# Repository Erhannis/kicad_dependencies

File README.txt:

Some component modules for KiCAD projects, like a micro usb power/data connection, or an eeprom chip with associated caps and resistors.  Comes as sheets, with separate areas of 4-layer PCB, and everything should be annotated with JLCPCB component IDs so you can export with their kicad plugin and it should autofill all the parts for assembly.

To use:
Copy the .kicad_sch file you want, into your project.
In KiCAD, copy the sheet block you want from this project into your project.
In KiCAD, ensure your project has 4 layers (MAYBE you can get it to work otherwise) then copy the corresponding chunk of PCB you want.
THEN "update pcb from schematic", to ensure everything synced up.

IF YOU ADD A MODULE, or rename a reference, you may need to run the vscode js script (see the nur::script extension) to get the refs to copy right - it updates all the labels from the pcb. ...I think.  I forget, now.  Then it removes the "instances" blocks, which don't seem to be necessary and can apparently gunk up the refs??  Commit your files before running the script.

If a part won't load for you, try `pip install easyeda2kicad` and `easyeda2kicad --lcsc_id LCSC_ID_HERE --full`, and adding its symbol/footprint folder to kicad.  I sometimes feel like it would be better to find a kicad built-in footprint or whatever, but it's just so easy....  (I don't think I've used this yet in this repo, but it's just a matter of time, haha.)

So far these things are like, MIT or CERN OHL v2 P (even if I've had to find a second source for the same decisions in a few places).

Notes:
(There may be bugs not listed here.)
inverted_regulator_12v doesn't quite manage an amp; it thermal cycles at 0.85A.  0.8A seemed to work, though you might do 0.7A to be safe.  If you added a proper heat sink it might manage MORE than 1A, haha.  Maybe you could add vias to a plane; depends on if the back is grounded; gnd is connected to -12V after all.
power_cell_18650_3s
  successfully provides several amps at ~12V
  successfully shuts down when batteries dip below 2.7V*3
  successfully switch on/off
  BUG: DO NOT short the output.  It kills the on/off transistor which shorts mostly closed, preventing the controller from turning off the circuit.  Further shorts can cause the on/off transistor to catch fire.
  BUG: it prevents overcurrent when charging (only lightly tested), but does not actually regulate the charging current!  Which means it can't charge the battery without external current control.  Sigh.
amp12v2a does not work.  Huge noise on the output.  I don't know why, I've been trying to get similar circuits to work for weeks.

-Erhannis

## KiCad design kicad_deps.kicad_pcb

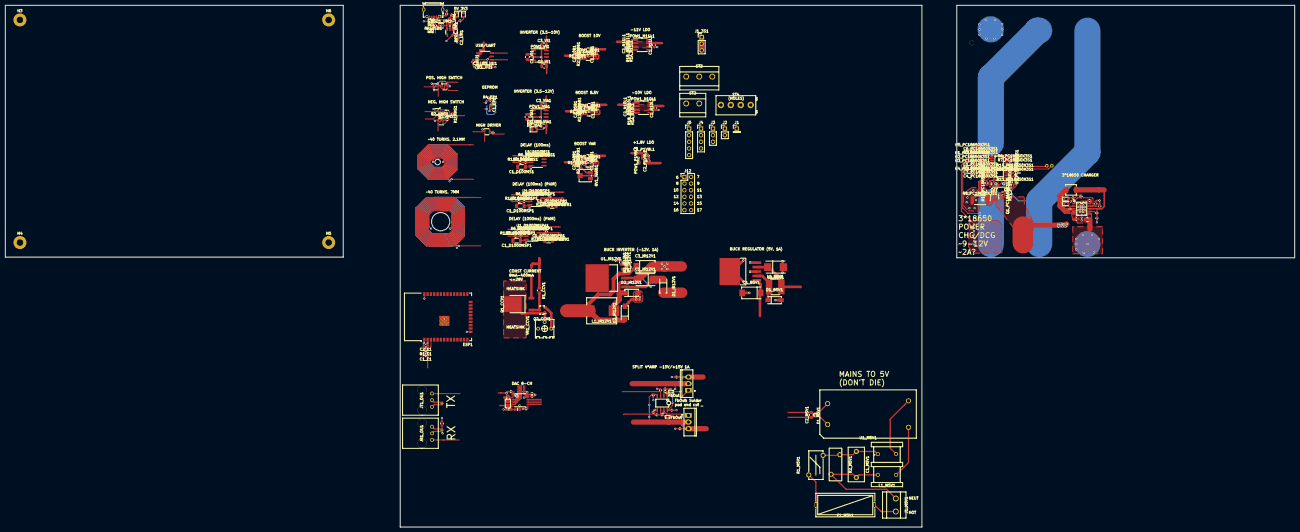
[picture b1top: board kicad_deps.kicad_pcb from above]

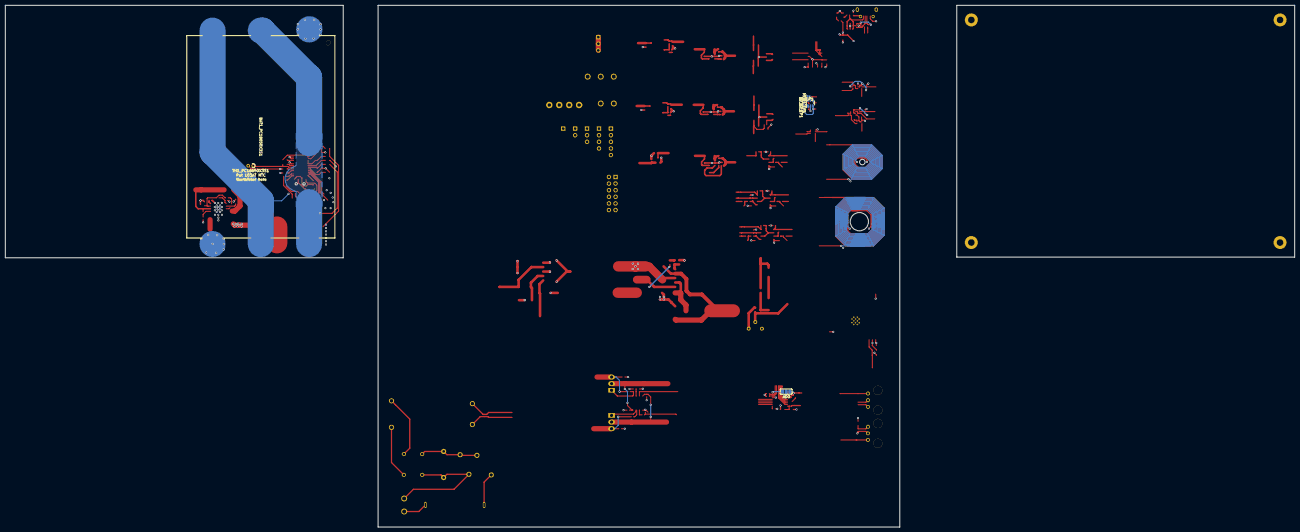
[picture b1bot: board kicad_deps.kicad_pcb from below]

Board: 4 copper layers, 200.0 x 200.0 mm, 232 parts (7 on the bottom side), 149 nets.

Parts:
BAT1_PC18650X3S1: BH-18650-B5BA016; BAT-SMD_BH-18650-B5BA016
C1_10B1, C1_85B1, C1_C18650X3S1, C1_N10L1, C1_N11L1, C1_P1V8L1, C1_VARB1, C2_10B1, C2_85B1, C2_C18650X3S1, C2_N10L1, C2_N11L1, C2_P1V8L1, C2_VARB1, C5_C18650X3S1: 10uF; C_0603_1608Metric
C1_B5V1: 100uF; CAP-SMD_L7.3-W4.3-R-RD
C1_D100MS1, C1_D100MSP1, C1_D100MSPB1, C1_D1000MSP1, C1_D1000MSPB1: 100uF; C_1206_3216Metric
C1_E1, C1_UU1, C2_UU1, C3_UU1, C5_PC18650X3S1, C6_PC18650X3S1: 1uF; C_0603_1608Metric
C1_EP1, C1_OU1, C2_OU1, C3_C18650X3S1: 100nF; C_0402_1005Metric
C1_IR12V1: 68uF; CASE-D_7343
C1_M5V1: 100nF/275V; C_Rect_L13.0mm_W6.0mm_P10.00mm_FKS3_FKP3_MKS4
C1_PC18650X3S1, C2_IR12V1, C2_PC18650X3S1, C3_PC18650X3S1, C4_PC18650X3S1: 0.1uF; C_0603_1608Metric
C1_S4AN15P151A1, C2_S4AN15P151A1: 0.1uF; C_0402_1005Metric
C1_UM1, C1_VI1, C1_VIA1, C2_M5V1, C2_UM1, C2_VI1, C2_VIA1, C3_VI1, C3_VIA1: 10uF; C_0805_2012Metric
C2_B5V1: 470uF; CASE-D_7343
C2_E1: 22uF; C_0603_1608Metric
C3_D8C1: 1uF; 0603-NO
C3_IR12V1: 47uF; CAP-SMD_L7.3-W4.3-FD
C4_C18650X3S1: C; C_0805_2012Metric
C4_D8C1: 0.1uF; 0603-NO
D1_10B1, D1_85B1, D1_VARB1, D1_VIA1: D_Schottky; D_0402_1005Metric
D1_B5V1, D1_IR12V1, D2_IR12V1, D3_IR12V1: SS54_C22452; SMA_L4.4-W2.8-LS5.4-R-RD
D1_M5V1: ESD9B5.0ST5G; D_SOD-923
D1_UM1: LED(R); LED_0603_1608Metric
D2_UM1: LED(G); LED_0603_1608Metric
D2_VIA1: D; D_0805_2012Metric
ESD1_UM1: USBLC6-2P6; SOT-666
ESP1: ESP32-WROOM-32D
F1_M5V1: Fuse transparent seat; FUSE-TH_L24.5-W9.8-P22.5
FB1_D8C1: FERRITE; 0603-NO
H1, H2: MountingHole; MountingHole_2.1mm
H3, H4, H5, H6: MountingHole_Pad; MountingHole_2.5mm_Pad
J1: Conn_01x01_Pin; PinHeader_1x01_P2.54mm_Vertical
J1_3S1, J3: Conn_01x03_Pin; PinHeader_1x03_P2.54mm_Vertical
J1_M5V1: XY126V-5.0-2P; CONN-TH_XY126V-5.0-2P
J2: Conn_01x02_Pin; PinHeader_1x02_P2.54mm_Vertical
J4: Conn_01x04_Pin; PinHeader_1x04_P2.54mm_Vertical
J5: Conn_01x05_Pin; PinHeader_1x05_P2.54mm_Vertical
J12: Conn_02x06_Odd_Even; PinHeader_2x06_P2.54mm_Vertical
JP1_S4AN15P151A1, JP2_S4AN15P151A1: SolderJumper_2_Open; SolderJumper-2_P0.5mm_Open_Pad0.5x0.5mm
JR1_OU1: ZGY135/T9(PLR); OPTO-TH_ZGY135-T9-PLR
JT1_OU1: ZGY133/T9(PLT); OPTO-TH_ZGY135-T9-PLR
L1_10B1, L1_85B1, L1_VARB1: L 10uH; L_0805_2012Metric
L1_B5V1: 330uH; IND-SMD_L6.0-W6.0_FNR60XXS
L1_C18650X3S1: SL0420-2R2M; IND-SMD_L4.5-W4.1_GSSM0420
L1_IR12V1: 33uH, 4A; IND-SMD_L11.5-W10.0_FXL1040
L1_M5V1: UU9.8-20MH; FILTER-TH_4P-L17.0-W12.0-P7.00-D0.6-S8.00
L1_OU1: 47uH; L_0603_1608Metric
LED1_C18650X3S1: LED(R); LED_0603_1608Metric
LED2_C18650X3S1: LED(B); LED_0603_1608Metric
MEM1_EP1: 93LCxxB; SOT-23-6
POW1_10B1, POW1_85B1, POW1_VARB1: LM27313XMF; SOT-23-5
POW1_N10L1, POW1_N11L1: LM337L_SO8; SOIC-8_3.9x4.9mm_P1.27mm
POW1_P1V8L1: APE8865N-18-HF-3; SOT-23
POW1_VI1, POW1_VIA1: TC7662Bx0A; SOIC-8_3.9x4.9mm_P1.27mm
Q1_CCV1: MOT13003D; TO-252-3_L6.5-W5.9-P4.60-LS10.0-BL
Q1_HD1, Q1_NHS1, Q1_PHS1, Q2_NHS1, Q2_PHS1, Q3_NHS1: BSD235C; SOT-363_SC-70-6
Q1_PC18650X3S1: FS8205A_C908265; SOT-23-6_L2.9-W1.6-P0.95-LS2.8-BR
Q1_S4AN15P151A1: IRF540NPBF; TO-220-3_L10.0-W4.5-P2.54-L
Q2_CCV1: SS8050; SOT-23-3
Q2_S4AN15P151A1: IRF9540NPBF; TO-220-3_L10.0-W4.5-P2.54-L
R1A_N10L1: R 1.6k 1%; R_0402_1005Metric
R1A_N11L1: R 1.8k 1%; R_0402_1005Metric
R1B_N10L1, R1B_N11L1: R 75 1%; R_0402_1005Metric
R1_10B1, R1_85B1, R1_VARB1: R 100k 1%; R_0402_1005Metric
R1_C18650X3S1: 37k; R_0402_1005Metric
R1_CCV1: 3.3k; R_0805_2012Metric
R1_D8C1, R1_D1000MSP1, R1_D1000MSPB1, R1_HD1, R1_S4AN15P151A1, R2_C18650X3S1, R2_D100MS1, R2_D100MSP1, R2_D100MSPB1, R2_D1000MSP1, R2_D1000MSPB1, R4_D100MS1, R4_D100MSP1, R4_D1000MSP1, R4_S4AN15P151A1, R5_D100MS1, R5_D100MSP1, R5_D1000MSP1, R5_S4AN15P151A1, R6_S4AN15P151A1: 10k; R_0402_1005Metric
R1_D100MS1, R1_D100MSP1, R1_D100MSPB1, R3_C18650X3S1: 1k; R_0402_1005Metric
R1_E1, R6_PC18650X3S1, R7_PC18650X3S1, R15_PC18650X3S1: 10k; R_0603_1608Metric
R1_EP1, R2_EP1, R4_EP1: 10K; R_0402_1005Metric
R1_IR12V1, R2_IR12V1: 47k; R_0603_1608Metric
R1_M5V1: 5D-9_C332361; RES-TH_L11.0-W5.5-P7.50-D0.8-S5.50
R1_NHS1, R2_S4AN15P151A1, R3_NHS1: 30k; R_0402_1005Metric
R1_PC18650X3S1, R2_PC18650X3S1, R3_PC18650X3S1, R4_PC18650X3S1: 75ohm; R_0603_1608Metric
R1_UM1: 1M; R_0402_1005Metric
R2_10B1: R 14k 1%; R_0402_1005Metric
R2_85B1: R 16k 1%; R_0402_1005Metric
R2_D8C1, R3_D8C1, R4_D8C1: 4.7k; R_0402_1005Metric
R2_M5V1: 471KD10; RES-TH_L12.5-W4.8-P7.50-D1.2-S3.40
R2_N10L1, R2_N11L1: R 240 1%; R_0402_1005Metric
R2_NHS1: 50k; R_0402_1005Metric
R2_UM1, R3_UM1: 27; R_0402_1005Metric
R2_VARB1: R 4.53k 1%; R_0402_1005Metric
R3_D100MS1, R3_D100MSP1, R3_D100MSPB1, R3_D1000MSP1, R3_D1000MSPB1: 10M; R_0402_1005Metric
R3_EP1: 2K; R_0402_1005Metric
R3_S4AN15P151A1: 40k; R_0402_1005Metric
R4_C18650X3S1, R5_C18650X3S1, R6_D100MS1, R6_D100MSP1, R6_D100MSPB1, R6_D1000MSP1, R6_D1000MSPB1, R7_S4AN15P151A1, R8_S4AN15P151A1: 100k; R_0402_1005Metric
R4_UM1, R5_UM1: 330; R_0402_1005Metric
R5_PC18650X3S1, R11_PC18650X3S1: 1k; R_0603_1608Metric
R6_C18650X3S1: 3k; R_0402_1005Metric
R8_PC18650X3S1: 10mOhm; R_2512_6332Metric
R9_PC18650X3S1, R10_PC18650X3S1: 1M; R_0603_1608Metric
R12_PC18650X3S1: 4.42k; R_0603_1608Metric
R13_PC18650X3S1: 450k; R_0402_1005Metric
R14_PC18650X3S1: 294k; R_0603_1608Metric
REG1_UM1: AP2112K-3.3; SOT-23-5
RP_USB1: MICROXNJ; MICRO-USB-SMD_MICROXNJ
RV1_VARB1: 100k R_Potentiometer; Potentiometer_Bourns_3314J_Vertical
SJ1_D8C1: SOLDERJUMPER_CLOSED; SOLDERJUMPER_CLOSEDWIRE
SJ3_D8C1: SOLDERJUMPER_2WAY; SOLDERJUMPER_2WAY_OPEN_NOPASTE
ST2: XY126V-5.0-2P; CONN-TH_XY126V-5.0-2P
ST3: XY126V-5.0-3P; CONN-TH_XY126V-5.0-3P
ST4: DB125-3.81-4P; CONN-TH_DB125-3.81-4P
SW1_PC18650X3S1: MSS3-Q-T/R; SW-SMD_MSS3-Q-T-R
TH1_PC18650X3S1: 103AT NTC 10k +-3%; R_Axial_DIN0204_L3.6mm_D1.6mm_P1.90mm_Vertical
U1_B5V1: LM2575S-5.0/TR; TO-263-5_L10.6-W9.6-P1.70-LS15.9-BR
U1_C18650X3S1: LGS5523; ESSOP-10_L4.9-W3.9-P1.00-LS6.0-BL-EP
U1_D100MS1, U1_D100MSP1, U1_D1000MSPA1: LM358; SOIC-8_3.9x4.9mm_P1.27mm
U1_IR12V1: LM2575HVS-12_C347430; TO-263-5_L10.2-W9.2-P1.70-BR
U1_M5V1: EC03-S05_C2840800; PWRM-TH_EC03-S05
U1_PC18650X3S1: BQ7791502PWR; TSSOP-24_L7.8-W4.4-P0.65-LS6.4-BL_1
U1_S4AN15P151A1: LM358; SOIC-8_L5.0-W4.0-P1.27-LS6.0-BL
U1_UU1: HT42B534_8SOP; SOP-8_3.9x4.9mm_P1.27mm
VR1_CCV1: 3362P-1-101LF; RES-ADJ-TH_3362P-1-104LF
X1_D8C1: DAC7578PW; TSSOP16

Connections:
+3V3: C1_EP1.1, C1_UU1.1, C2_E1.1, C2_OU1.2, C2_UM1.1, C3_UU1.1, ESP1.2 (VDD), JT1_OU1.2 (VCC), L1_OU1.1, MEM1_EP1.6 (VCC), R1_E1.2, R1_EP1.2, R2_EP1.2, R4_EP1.2, R5_UM1.1, REG1_UM1.5 (VOUT), U1_UU1.3 (VDDIO), U1_UU1.7 (VDD)
/DC Boost 8.5v/VIN: C1_85B1.2, L1_85B1.1, POW1_85B1.4 (EN), POW1_85B1.5 (VIN)
/DC Boost 8.5v/VOUT: C2_85B1.2, D1_85B1.1 (K), R1_85B1.1
/DC Boost 10v/VIN: C1_10B1.2, L1_10B1.1, POW1_10B1.4 (EN), POW1_10B1.5 (VIN)
/DC Boost 10v/VOUT: C2_10B1.2, D1_10B1.1 (K), R1_10B1.1
/DC Boost Var/VIN: C1_VARB1.2, L1_VARB1.1, POW1_VARB1.4 (EN), POW1_VARB1.5 (VIN)
/DC Boost Var/VOUT: C2_VARB1.2, D1_VARB1.1 (K), R1_VARB1.1
/Delay (100ms) (pair)/VDD: R4_D100MSP1.1, U1_D100MSP1.8 (V+)
/Delay (100ms) (pair)/VOUT1: R3_D100MSP1.2, R6_D100MSP1.2, U1_D100MSP1.1
/Delay (100ms) (pair)/VOUT2: R3_D100MSPB1.2, R6_D100MSPB1.2, U1_D100MSP1.7
/Delay (100ms)/VDD: R4_D100MS1.1, U1_D100MS1.8 (V+)
/Delay (100ms)/VOUT1: R3_D100MS1.2, R6_D100MS1.2, U1_D100MS1.1
/Delay (1000ms) (pair)/VDD: R4_D1000MSP1.1, U1_D1000MSPA1.8 (V+)
/Delay (1000ms) (pair)/VOUT1: R3_D1000MSP1.2, R6_D1000MSP1.2, U1_D1000MSPA1.1
/Delay (1000ms) (pair)/VOUT2: R3_D1000MSPB1.2, R6_D1000MSPB1.2, U1_D1000MSPA1.7
/EEPROM/CLK: MEM1_EP1.4 (CLK), R4_EP1.1
/EEPROM/CS#: MEM1_EP1.5 (CS), R1_EP1.1
/EEPROM/DATA: MEM1_EP1.3 (DI), R3_EP1.1
/ESP32/EN: C1_E1.1, ESP1.3 (EN), R1_E1.1
/High Driver/V_IN: Q1_HD1.4 (SP), R1_HD1.2
/Mains to 5V/+5V: C2_M5V1.2, D1_M5V1.1 (A1), U1_M5V1.5 (+Vo)
/Mains to 5V/GND: C2_M5V1.1, D1_M5V1.2 (A2), U1_M5V1.3 (-Vo)
/Mains to 5V/HOT: F1_M5V1.1, J1_M5V1.2
/Mains to 5V/NEUTRAL: C1_M5V1.2, J1_M5V1.1, L1_M5V1.4, R2_M5V1.2
/Negative High Switch/TREF: Q1_NHS1.4 (SP), Q2_NHS1.4 (SP)
/Negative High Switch/TRIG: Q1_NHS1.2 (GN), Q1_NHS1.5 (GP)
/Negative High Switch/V_IN: Q2_NHS1.1 (SN), Q3_NHS1.1 (SN), R1_NHS1.2, R3_NHS1.2
/Negative LDO -10v/-VIN: C1_N10L1.2, POW1_N10L1.2 (VI), POW1_N10L1.3 (VI), POW1_N10L1.6 (VI), POW1_N10L1.7 (VI)
/Negative LDO -10v/-VOUT: C2_N10L1.2, POW1_N10L1.1 (VO), R2_N10L1.2
/Negative LDO -11v/-VIN: C1_N11L1.2, POW1_N11L1.2 (VI), POW1_N11L1.3 (VI), POW1_N11L1.6 (VI), POW1_N11L1.7 (VI)
/Negative LDO -11v/-VOUT: C2_N11L1.2, POW1_N11L1.1 (VO), R2_N11L1.2
/Positive High Switch/TRIG: Q1_PHS1.2 (GN), Q1_PHS1.5 (GP)
/Positive High Switch/V_OUT: Q2_PHS1.3 (DP), Q2_PHS1.6 (DN)
/Positive LDO +1.8v/VIN: C1_P1V8L1.1, POW1_P1V8L1.3 (VI)
/Positive LDO +1.8v/VOUT: C2_P1V8L1.1, POW1_P1V8L1.2 (VO)
/Splitter(3)/IN: J1_3S1.1, J1_3S1.2, J1_3S1.3
/USB Micro B/+5V: C1_UM1.1, ESD1_UM1.5 (VBUS), R4_UM1.1, REG1_UM1.1 (VIN), REG1_UM1.3 (EN), RP_USB1.1 (VBUS)
/Voltage Inverter alt/V+: C3_VIA1.2, POW1_VIA1.8 (V+)
/Voltage Inverter alt/V-: C2_VIA1.2, D1_VIA1.2 (A), D2_VIA1.2 (A), POW1_VIA1.5 (VOUT)
/Voltage Inverter/V+: C3_VI1.2, POW1_VI1.8 (V+)
/Voltage Inverter/V-: C2_VI1.2, POW1_VI1.5 (VOUT)
/buck_5v/Vin: C1_B5V1.1, U1_B5V1.1 (VIN)
/buck_5v/Vout: C2_B5V1.1, L1_B5V1.2, U1_B5V1.4 (FB)
/charger_18650_3s/Vin: C5_C18650X3S1.1, L1_C18650X3S1.1, R1_C18650X3S1.1, U1_C18650X3S1.8 (VIN)
/dac8c/SCL: R4_D8C1.2, X1_D8C1.16 (SCL)
/dac8c/SDA: R3_D8C1.2, X1_D8C1.15 (SDA)
/dac8c/VREFIN: C3_D8C1.1, C4_D8C1.1, SJ1_D8C1.1, X1_D8C1.8 (VREFIN)
/dac8c/Vcc: FB1_D8C1.2, R1_D8C1.1, R2_D8C1.1, R3_D8C1.1, R4_D8C1.1, SJ3_D8C1.1, X1_D8C1.3 (AVDD)
/dac8c/~CLR: R1_D8C1.2, X1_D8C1.9 (~CLR)
/dac8c/~LDAC: R2_D8C1.2, X1_D8C1.1 (~LDAC)
/inverted_regulator_12v/Vout: C1_IR12V1.2, C3_IR12V1.2, D2_IR12V1.1 (A), D3_IR12V1.1 (A), R2_IR12V1.1, U1_IR12V1.3 (GND)
/power_cell_18650_3s/cell1-: BAT1_PC18650X3S1.1, C3_PC18650X3S1.2, C4_PC18650X3S1.1, C5_PC18650X3S1.2, C6_PC18650X3S1.1, R4_PC18650X3S1.1, R8_PC18650X3S1.1, R14_PC18650X3S1.2, R15_PC18650X3S1.2, TH1_PC18650X3S1.2, U1_PC18650X3S1.9 (VSS), U1_PC18650X3S1.10 (SRP), U1_PC18650X3S1.20 (CCFG), U1_PC18650X3S1.23 (CTRC), U1_PC18650X3S1.24 (CTRD)
/power_cell_18650_3s/cell3+: BAT1_PC18650X3S1.6, C4_C18650X3S1.1, R1_PC18650X3S1.1, R5_PC18650X3S1.1, U1_C18650X3S1.6 (BAT)
/power_cell_18650_3s/cell12: BAT1_PC18650X3S1.2, BAT1_PC18650X3S1.3, R3_PC18650X3S1.1
/power_cell_18650_3s/cell23: BAT1_PC18650X3S1.4, BAT1_PC18650X3S1.5, R2_PC18650X3S1.1
/split_4xamp_n15p15_1a/LOAD+: JP1_S4AN15P151A1.2 (B), Q1_S4AN15P151A1.3 (S), R4_S4AN15P151A1.2
/split_4xamp_n15p15_1a/LOAD-: JP2_S4AN15P151A1.2 (B), Q2_S4AN15P151A1.3 (S), R6_S4AN15P151A1.2
/split_4xamp_n15p15_1a/Sig1: R8_S4AN15P151A1.1, U1_S4AN15P151A1.3 (+)
/split_4xamp_n15p15_1a/Sig2: R5_S4AN15P151A1.2, R7_S4AN15P151A1.1
/split_4xamp_n15p15_1a/Vcc: C1_S4AN15P151A1.1, Q1_S4AN15P151A1.2 (D), U1_S4AN15P151A1.8 (V+)
/split_4xamp_n15p15_1a/Vee: C2_S4AN15P151A1.1, Q2_S4AN15P151A1.2 (D), U1_S4AN15P151A1.4 (V-)
GND: C1_10B1.1, C1_85B1.1, C1_B5V1.2, C1_C18650X3S1.1, C1_D100MS1.1, C1_D100MSP1.1, C1_D100MSPB1.1, C1_D1000MSP1.1, C1_D1000MSPB1.1, C1_E1.2, C1_EP1.2, C1_N10L1.1, C1_N11L1.1, C1_OU1.2, C1_P1V8L1.2, C1_S4AN15P151A1.2, C1_UM1.2, C1_UU1.2, C1_VARB1.1, C2_10B1.1, C2_85B1.1, C2_B5V1.2, C2_C18650X3S1.2, C2_E1.2, C2_N10L1.1, C2_N11L1.1, C2_OU1.1, C2_P1V8L1.2, C2_S4AN15P151A1.2, C2_UM1.2, C2_UU1.2, C2_VARB1.1, C2_VI1.1, C2_VIA1.1, C3_D8C1.2, C3_IR12V1.1, C3_UU1.2, C3_VI1.1, C3_VIA1.1, C4_C18650X3S1.2, C4_D8C1.2, C5_C18650X3S1.2, D1_B5V1.1 (A), D1_UM1.1 (K), D2_UM1.1 (K), D2_VIA1.1 (K), D3_IR12V1.2 (K), ESD1_UM1.2 (GND), ESP1.1 (GND), ESP1.15 (GND), ESP1.38 (GND), ESP1.39 (GND), H3.1, H4.1, H5.1, H6.1, JR1_OU1.2 (GND), JT1_OU1.1 (GND), L1_IR12V1.2, LED2_C18650X3S1.1 (K), MEM1_EP1.2 (GND), POW1_10B1.2 (GND), POW1_85B1.2 (GND), POW1_P1V8L1.1 (GND), POW1_VARB1.2 (GND), POW1_VI1.3 (GND), POW1_VIA1.3 (GND), Q1_HD1.1 (SN), Q1_NHS1.1 (SN), Q1_PC18650X3S1.3 (S2), Q1_PHS1.1 (SN), Q2_CCV1.2 (E), Q2_PHS1.1 (SN), Q3_NHS1.4 (SP), R1A_N10L1.1, R1A_N11L1.1, R1_S4AN15P151A1.1, R1_UM1.1, R2_10B1.2, R2_85B1.2, R2_C18650X3S1.2, R2_NHS1.1, R2_VARB1.2, R3_C18650X3S1.1, R4_C18650X3S1.1, R4_S4AN15P151A1.1, R5_D100MS1.2, R5_D100MSP1.2, R5_D1000MSP1.2, R6_D100MS1.1, R6_D100MSP1.1, R6_D100MSPB1.1, R6_D1000MSP1.1, R6_D1000MSPB1.1, R6_S4AN15P151A1.1, R7_S4AN15P151A1.2, R8_S4AN15P151A1.2, R10_PC18650X3S1.2, R13_PC18650X3S1.1, REG1_UM1.2 (GND), RP_USB1.5 (GND), SJ3_D8C1.3, U1_B5V1.3 (GND), U1_B5V1.5 (#ON/OFF), U1_B5V1.6 (GND), U1_C18650X3S1.11 (GND), U1_D100MS1.4 (V-), U1_D100MSP1.4 (V-), U1_D1000MSPA1.4 (V-), U1_IR12V1.4 (FB), U1_S4AN15P151A1.5 (+), U1_UU1.1 (GND), VR1_CCV1.3, X1_D8C1.14 (GND)
unnamed: C1_D100MS1.2, R1_D100MS1.2, R2_D100MS1.1
unnamed: C1_D100MSP1.2, R1_D100MSP1.2, R2_D100MSP1.1
unnamed: C1_D100MSPB1.2, R1_D100MSPB1.2, R2_D100MSPB1.1
unnamed: C1_D1000MSP1.2, R1_D1000MSP1.2, R2_D1000MSP1.1
unnamed: C1_D1000MSPB1.2, R1_D1000MSPB1.2, R2_D1000MSPB1.1
unnamed: C1_M5V1.1, L1_M5V1.1, R1_M5V1.2, R2_M5V1.1
unnamed: C2_IR12V1.2, R1_IR12V1.1
unnamed: D1_10B1.2 (A), L1_10B1.2, POW1_10B1.1 (SW)
unnamed: D1_85B1.2 (A), L1_85B1.2, POW1_85B1.1 (SW)
unnamed: D1_B5V1.2 (K), L1_B5V1.1, U1_B5V1.2 (OUTPUT)
unnamed: C1_IR12V1.1, C2_IR12V1.1, D1_IR12V1.2 (K), U1_IR12V1.1 (VIN)
unnamed: D1_UM1.2 (A), R4_UM1.2
unnamed: D1_VARB1.2 (A), L1_VARB1.2, POW1_VARB1.1 (SW)
unnamed: C1_VIA1.2, D1_VIA1.1 (K), POW1_VIA1.4 (CAP-)
unnamed: D2_IR12V1.2 (K), L1_IR12V1.1, U1_IR12V1.2 (OUT)
unnamed: D2_UM1.2 (A), R5_UM1.2
unnamed: F1_M5V1.2, R1_M5V1.1
unnamed: FB1_D8C1.1, SJ1_D8C1.2
unnamed: JP1_S4AN15P151A1.1 (A), Q1_S4AN15P151A1.1 (G), R2_S4AN15P151A1.1, U1_S4AN15P151A1.1
unnamed: JP2_S4AN15P151A1.1 (A), Q2_S4AN15P151A1.1 (G), R3_S4AN15P151A1.1, U1_S4AN15P151A1.7
unnamed: C1_OU1.1, JR1_OU1.3 (VCC), L1_OU1.2
unnamed: LED1_C18650X3S1.2 (A), LED2_C18650X3S1.2 (A), R6_C18650X3S1.2
unnamed: LED1_C18650X3S1.1 (K), U1_C18650X3S1.2 (LED)
unnamed: MEM1_EP1.1 (DO), R2_EP1.1, R3_EP1.2
unnamed: POW1_10B1.3 (FB), R1_10B1.2, R2_10B1.1
unnamed: POW1_85B1.3 (FB), R1_85B1.2, R2_85B1.1
unnamed: POW1_N10L1.4 (ADJ), R1B_N10L1.2, R2_N10L1.1
unnamed: POW1_N11L1.4 (ADJ), R1B_N11L1.2, R2_N11L1.1
unnamed: POW1_VARB1.3 (FB), R1_VARB1.2, RV1_VARB1.2
unnamed: C1_VI1.1, POW1_VI1.2 (CAP+)
unnamed: C1_VI1.2, POW1_VI1.4 (CAP-)
unnamed: C1_VIA1.1, POW1_VIA1.2 (CAP+)
unnamed: Q1_CCV1.1 (B), Q2_CCV1.3 (C), R1_CCV1.2
unnamed: Q1_CCV1.2 (E), Q2_CCV1.1 (B), VR1_CCV1.2
unnamed: Q1_HD1.5 (GP), Q1_HD1.6 (DN), R1_HD1.1
unnamed: Q1_NHS1.3 (DP), Q1_NHS1.6 (DN), Q2_NHS1.5 (GP)
unnamed: Q1_PC18650X3S1.2 (D1/D2), Q1_PC18650X3S1.5 (D1/D2)
unnamed: Q1_PC18650X3S1.6 (G1), R9_PC18650X3S1.1, SW1_PC18650X3S1.2
unnamed: Q1_PC18650X3S1.4 (G2), R10_PC18650X3S1.1, R11_PC18650X3S1.1
unnamed: Q1_PC18650X3S1.1 (S1), R8_PC18650X3S1.2, R9_PC18650X3S1.2, SW1_PC18650X3S1.1, U1_PC18650X3S1.11 (SRN)
unnamed: Q1_PHS1.3 (DP), Q1_PHS1.6 (DN), Q2_PHS1.2 (GN), Q2_PHS1.5 (GP)
unnamed: Q2_NHS1.6 (DN), Q3_NHS1.5 (GP), R2_NHS1.2
unnamed: Q2_NHS1.2 (GN), Q2_NHS1.3 (DP), R1_NHS1.1
unnamed: Q3_NHS1.2 (GN), Q3_NHS1.3 (DP), R3_NHS1.1
unnamed: R1A_N10L1.2, R1B_N10L1.1
unnamed: R1A_N11L1.2, R1B_N11L1.1
unnamed: R2_VARB1.1, RV1_VARB1.3
unnamed: R12_PC18650X3S1.1, SW1_PC18650X3S1.3
unnamed: ESD1_UM1.1 (I/O1), ESD1_UM1.6 (I/O1), R2_UM1.2, RP_USB1.3 (D+)
unnamed: ESD1_UM1.3 (I/O2), ESD1_UM1.4 (I/O2), R3_UM1.2, RP_USB1.2 (D-)
unnamed: R1_UM1.2, RP_USB1.9 (SH4)
unnamed: C3_C18650X3S1.1, U1_C18650X3S1.3 (BST)
unnamed: R4_C18650X3S1.2, R5_C18650X3S1.2, U1_C18650X3S1.1 (EN/NTC)
unnamed: R3_C18650X3S1.2, U1_C18650X3S1.10 (ISET)
unnamed: C3_C18650X3S1.2, L1_C18650X3S1.2, U1_C18650X3S1.4 (SW)
unnamed: C1_C18650X3S1.2, R5_C18650X3S1.1, R6_C18650X3S1.1, U1_C18650X3S1.9 (VCC)
unnamed: R1_C18650X3S1.2, R2_C18650X3S1.1, U1_C18650X3S1.7 (VHOLD)
unnamed: C2_C18650X3S1.1, U1_C18650X3S1.5 (VOUT)
unnamed: R2_D100MS1.2, R3_D100MS1.1, U1_D100MS1.3 (+)
unnamed: R4_D100MS1.2, R5_D100MS1.1, U1_D100MS1.2 (-)
unnamed: R2_D100MSP1.2, R3_D100MSP1.1, U1_D100MSP1.3 (+)
unnamed: R4_D100MSP1.2, R5_D100MSP1.1, U1_D100MSP1.2 (-), U1_D100MSP1.6 (-)
unnamed: R2_D100MSPB1.2, R3_D100MSPB1.1, U1_D100MSP1.5 (+)
unnamed: R2_D1000MSP1.2, R3_D1000MSP1.1, U1_D1000MSPA1.3 (+)
unnamed: R4_D1000MSP1.2, R5_D1000MSP1.1, U1_D1000MSPA1.2 (-), U1_D1000MSPA1.6 (-)
unnamed: R2_D1000MSPB1.2, R3_D1000MSPB1.1, U1_D1000MSPA1.5 (+)
unnamed: R1_IR12V1.2, R2_IR12V1.2, U1_IR12V1.5 (~ON/OFF)
unnamed: L1_M5V1.2, U1_M5V1.1 (AC(L))
unnamed: L1_M5V1.3, U1_M5V1.2 (AC(N))
unnamed: C6_PC18650X3S1.2, U1_PC18650X3S1.2 (AVDD)
unnamed: R15_PC18650X3S1.1, U1_PC18650X3S1.16 (CBI)
unnamed: R11_PC18650X3S1.2, U1_PC18650X3S1.13 (CHG)
unnamed: R12_PC18650X3S1.2, U1_PC18650X3S1.12 (DSG)
unnamed: R13_PC18650X3S1.2, U1_PC18650X3S1.14 (LD)
unnamed: R14_PC18650X3S1.1, U1_PC18650X3S1.17 (OCDP)
unnamed: R6_PC18650X3S1.1, U1_PC18650X3S1.22 (PRES)
unnamed: R7_PC18650X3S1.2, TH1_PC18650X3S1.1, U1_PC18650X3S1.18 (TS)
unnamed: C2_PC18650X3S1.2, C3_PC18650X3S1.1, R3_PC18650X3S1.2, U1_PC18650X3S1.7 (VC1)
unnamed: C1_PC18650X3S1.2, C2_PC18650X3S1.1, R2_PC18650X3S1.2, U1_PC18650X3S1.6 (VC2)
unnamed: C1_PC18650X3S1.1, R1_PC18650X3S1.2, U1_PC18650X3S1.3 (VC5), U1_PC18650X3S1.4 (VC4), U1_PC18650X3S1.5 (VC3)
unnamed: C4_PC18650X3S1.2, R4_PC18650X3S1.2, U1_PC18650X3S1.8 (VCO)
unnamed: C5_PC18650X3S1.1, R5_PC18650X3S1.2, R6_PC18650X3S1.2, U1_PC18650X3S1.1 (VDD)
unnamed: R7_PC18650X3S1.1, U1_PC18650X3S1.19 (VTB)
unnamed: R1_S4AN15P151A1.2, R2_S4AN15P151A1.2, U1_S4AN15P151A1.2 (-)
unnamed: R3_S4AN15P151A1.2, R5_S4AN15P151A1.1, U1_S4AN15P151A1.6 (-)
unnamed: C2_UU1.1, U1_UU1.8 (V33O)
unnamed: SJ3_D8C1.2, X1_D8C1.2 (ADDR0)

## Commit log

2023-08-09 Making a set of kicad 'dependencies', little sheets of various reused function
2023-08-13 Swapped out weird symbols for built-in ones
2023-08-13 Added pcb layouts for the modules
2023-08-13 Added sources
2023-08-13 Added readme.
2023-08-16 Added a voltage inverter
2023-08-16 Forgot to connect gnd
2023-08-16 Moved things around a little
2023-08-16 DC boost converter
2023-08-16 8.5v and 10v flavors of boost converter
2023-08-16 Man, copying and remapping layouts is a pain
2023-08-16 Standardized gnd pin dirs as 'provided' not 'current direction'
2023-08-16 Alternative inverter
2023-08-16 Laid out alternate inverter
2023-08-17 Negative LDO
2023-08-17 Two example negative LDO
2023-08-17 Ok, passed pcb checker
2023-08-17 Fiddling
2023-08-17 Splitter
2023-08-17 Trying to fix the refs
2023-08-17 update pcb
2023-08-17 Ok, I think maybe the refs are sanitized for copying
2023-08-18 It finally worked?!? MAN! That was stupid hard to just rename some components and be able to copy a sheet to another project. And I'm probably going to end up with weird glitches or something later. 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
2023-08-18 Forgot to revert a debug
2023-08-18 Added blank second 2-zone pcb board
2023-08-18 Added 1v8 LDO. Also a number of files appear to have changed?
2023-08-18 Sigh. Apparently I have to run that ref-fix script every time I add parts, now. Sheesh. At least it works.
2023-08-18 Except it DIDN'T. But I think it's fixed, now.
2023-10-08 Added delay and switch components
2023-10-10 Added 1000ms delay circuit. Also, UGH, the references are messed up on copy, again
2023-10-10 Dunno
2023-10-10 Is this better?
2023-10-10 Again
2023-10-10 GOSH DANG IT, REFERENCE SQUIRRELINESS
2023-10-18 Dunno what these changes are
2023-10-20 Updated note in accordance with experiment
2023-10-20 Added high driver, and some notes
2023-10-23 Normalized names
2023-10-23 Sigh, didn't quite work
2023-10-23 Trying again
2023-11-09 Added DC Boost Var
2023-11-09 Name normalization
2024-01-08 Added power LEDs to usb block
2024-01-08 Added USB/UART block
2024-01-08 Normalized references
2024-01-12 Added mains_to_5v
2024-01-12 Tweaks probably
2024-01-12 Normalization
2024-01-12 Removed orphaned GND. Probably kicad redid cached values, too.
2024-04-14 BROKEN Blehhhh, dangit kicad why your reference system kinda suck
2024-04-28 Updated kicad
2024-04-28 Oh and also these files
2024-04-28 Updated pcb from schematic, placed free headers
2024-05-09 Added a constant current driver. Proably overspecd.
2024-07-11 Added fiber optic uart module. Swapped out of stock LED.
2025-03-14 Updated to kicad 9 nightly. Added a 18650 power cell controller.
2025-03-14 Ok, fixed some errors the DRC found; I think now it might be done
2025-03-14 BROKEN Adding an on/off switch. ...I'm gonna end up with stupid transient crosstalk, aren't I.
2025-03-14 Moved the switch into a...sortof more convenient location
2025-03-15 Added buck inverter
2025-03-15 Added 5v buck regulator
2025-03-15 It borked my IDs, had to fix. Also I messed up the traces on the buck inverter, I think it woulda sent too much current through the fb trace.
2025-03-15 Ok, I think I fixed everything
2025-03-15 Added DAC
2025-03-16 Added slightly questionable amplifier
2025-03-16 Oops; fixing module ids
2025-03-16 Fixed module ids
2025-06-07 Added some notes, like things that don't work. Also all the files changed?
2025-06-10 Added split 4*amp
2025-06-10 Comment
2025-06-10 Added a charger circuit for the 18650s.
2025-06-12 Swapped out-of-stock parts, fixed missing part numbers
